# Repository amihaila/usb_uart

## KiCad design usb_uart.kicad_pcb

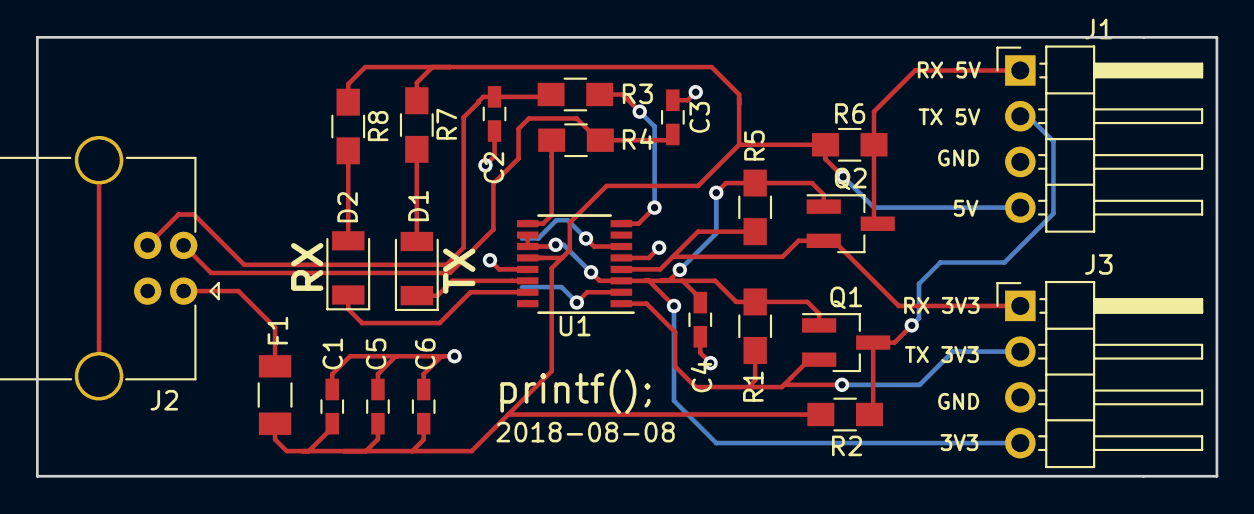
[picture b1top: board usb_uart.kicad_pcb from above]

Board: 2 copper layers, 65.5 x 24.4 mm, 24 parts (1 on the bottom side), 18 nets.

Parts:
C1: 10nF; C_0603_HandSoldering
C2, C3: 47pF; C_0603_HandSoldering
C4, C5: 100nF; C_0603_HandSoldering
C6: 4.7uF; C_0603_HandSoldering
D1, D2: LED; LED_1206_3216Metric_Pad1.07x1.80mm_HandSolder
F1: Polyfuse_Small; Fuse_1206_3216Metric_Pad1.24x1.80mm_HandSolder
J1, J3: Conn_01x04_Female; PinHeader_1x04_P2.54mm_Horizontal
J2: USB_B; USB_B_Horizontal
Q1, Q2: DMG2302UK; SOT-23_Handsoldering
R1, R2, R5, R6: 10K; R_0805_HandSoldering
R3, R4: 27R; R_0805_HandSoldering
R7, R8: 270R; R_0805_HandSoldering
R9: 0; R_0805_HandSoldering
U1: FT230FX; SSOP-16_3.9x4.9mm_P0.635mm

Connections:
+3V3: C4.1, J3.4, Q1.1, Q2.1, R1.1, R5.1, U1.3, U1.10, U1.11
+5V: C1.1, C5.1, C6.1, F1.1, J1.4, R2.1, R6.1, R7.1, R8.1, U1.12
/RX3V3: J3.1, Q2.2, R5.2, U1.4
/RX5V: J1.1, Q2.3, R6.2
/RXLED: D2.1, U1.15
/TX3V3: J3.2, Q1.2, R1.2, U1.1
/TX5V: J1.2, Q1.3, R2.2
/TXLED: D1.1, U1.14
GND: C1.2, C2.2, C3.2, C4.2, C5.2, C6.2, J1.3, J2.4, J3.3, U1.5, U1.13
unnamed: C2.1, J2.3, R3.2
unnamed: C3.1, J2.2, R4.2
unnamed: D1.2, R7.2
unnamed: D2.2, R8.2
unnamed: F1.2, J2.1
unnamed: R3.1, U1.8
unnamed: R4.1, U1.9
unnamed: R9.1, U1.6
unnamed: R9.2, U1.2

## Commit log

2018-08-07 Initial schematic
    USB/UART interface schematic
2018-08-07 add gitignore
2018-08-09 First draft pcb
    TODO: fix the rts/cts signals
